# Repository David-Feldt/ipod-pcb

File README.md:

# E-ink Spotify iPod

A pocket Spotify remote with an e-paper screen. It shows what's playing (with
dithered album art), and its buttons and thumbwheel control playback and volume
on whichever device Spotify is playing on. It has no speaker or headphone jack.

## At a glance

| | |
|---|---|
| Chip | ESP32-S3-MINI-1-N8 (Wi-Fi + Bluetooth LE, 8 MB flash) |
| Screen | 2.13-inch GDEY0213B74 e-paper, 122 × 250, portrait |
| Controls | Five buttons and an absolute volume thumbwheel |
| Power | USB-C charging, 1S LiPo |
| Board | Revision E, 42 × 98 mm, four layers, four M2.5 mounting holes |
| Status | Board 1 is built and running the firmware |

## What it does

- **Now playing:** title, artist, progress and album art, from the Spotify Web API
  over Wi-Fi.
- **Controls:** play/pause, previous/next track, and wheel volume.
- **Easy setup:** a Wi-Fi setup hotspot, then Spotify sign-in from your phone.
- **Bluetooth fallback:** when Wi-Fi is out of range, it works as a Bluetooth
  media remote for your phone.
- **Battery care:** shows a "Battery low" screen and sleeps when the battery runs
  down.

## Repository guide

| Path | What's there |
|---|---|
| `firmware/remote/` | ESP-IDF application firmware: build and usage in its README |
| `kicad/` | KiCad 10 project, generated schematic and PCB, check reports |
| `gen/` | Python generators for the schematic, placement, routing and outputs |
| `fab/` | Gerbers, BOM, placement file, printable schematic, ordering notes |
| `pairing/` | Static sign-in bounce page used during Spotify pairing |
| `renders/`, `photos/` | Board renders and photos of the built device |
| `review/` | Hardware review evidence and datasheets |

| Document | Read it for |
|---|---|
| `DESIGN.md` | GPIO map, power architecture, revision notes |
| `FIRMWARE-NOTES.md` | Hardware rules the firmware must follow (charger, battery, wheel, display) |
| `BRINGUP.md` | Bring-up procedure and bench log |
| `DEBUG.md` | Debug links, pads and headers |
| `MECHANICAL.md` | Verified dimensions and enclosure fit |
| `ORDER-READINESS.md` | What must be checked before ordering boards |

## Getting started

```sh
git clone https://github.com/David-Feldt/ipod-pcb.git
cd ipod-pcb
```

Everything current is on `main`. The older 1.54-inch, 40 × 78 mm design is
tagged `v1-1.54in`. The `portrait-2.13` branch keeps the development history of
the 2.13-inch revision.

To open the board, close any running KiCad editors and open
`kicad/eink-pod.kicad_pro`.

## Rebuilding the board

Requires KiCad 10, Python 3, Java and `tools/freerouting.jar`.

```sh
./build.sh        # regenerate schematic, PCB, routing, fab files and renders
./check-order.sh  # pre-order gate: automated checks plus pending reviews
```

`build.sh` runs ERC, routing, DRC, schematic parity and critical-route checks,
and stops if any of them fails. Don't edit the generated KiCad files by hand:
the next build overwrites them. Edit the generators instead:

| Change | Edit |
|---|---|
| Circuit | `gen/build_sch.py` |
| Placement | `gen/build_pcb.py` |
| USB, decoupling and boost wiring | `gen/critical_routes.py` (checked by `gen/verify_board.py`) |

Don't run two builds at once or rebuild while an editor is saving the board.

## Ordering

Run `./check-order.sh` first and record external evidence in
`order-review.json`. Things to choose at the fab (details in `fab/README.md`):

- **Stackup:** JLC04161H-7628, four layers, 1.6 mm, with a 90-ohm differential
  target for USB.
- **Vias:** epoxy-filled and copper-capped. This design has vias in thermal pads,
  so ordinary tenting won't do.
- **Assembly:** both sides. Check every rotation in the assembler's preview
  against `fab/assembly-pin1.csv`. Take extra care with the MOSFETs, USB-C, FPC
  connector and slide switch.

| Layer | Use |
|---|---|
| F.Cu | Buttons, charge LED, USB pair, signals, GND pour |
| In1.Cu | GND plane, reference for the USB pair |
| In2.Cu | 3.3 V plane |
| B.Cu | Main components, signals, GND pour |

## Building and testing a board

- **Battery:** use a protected 1S LiPo rated for at least 250 mA charging, and
  check the JST lead polarity before plugging it in.
- **Mounting:** front screw heads or bosses at the top two holes must stay within
  4.5 mm diameter to clear the display glass. Use a nylon screw in the top-right
  hole, next to the antenna.
- **Test:** USB in both orientations, Wi-Fi during low battery and screen
  refresh, sleep current, charging temperature, and radio range in the assembled
  case.

See `BRINGUP.md` for the full procedure and `DEBUG.md` for the debug links and
headers.

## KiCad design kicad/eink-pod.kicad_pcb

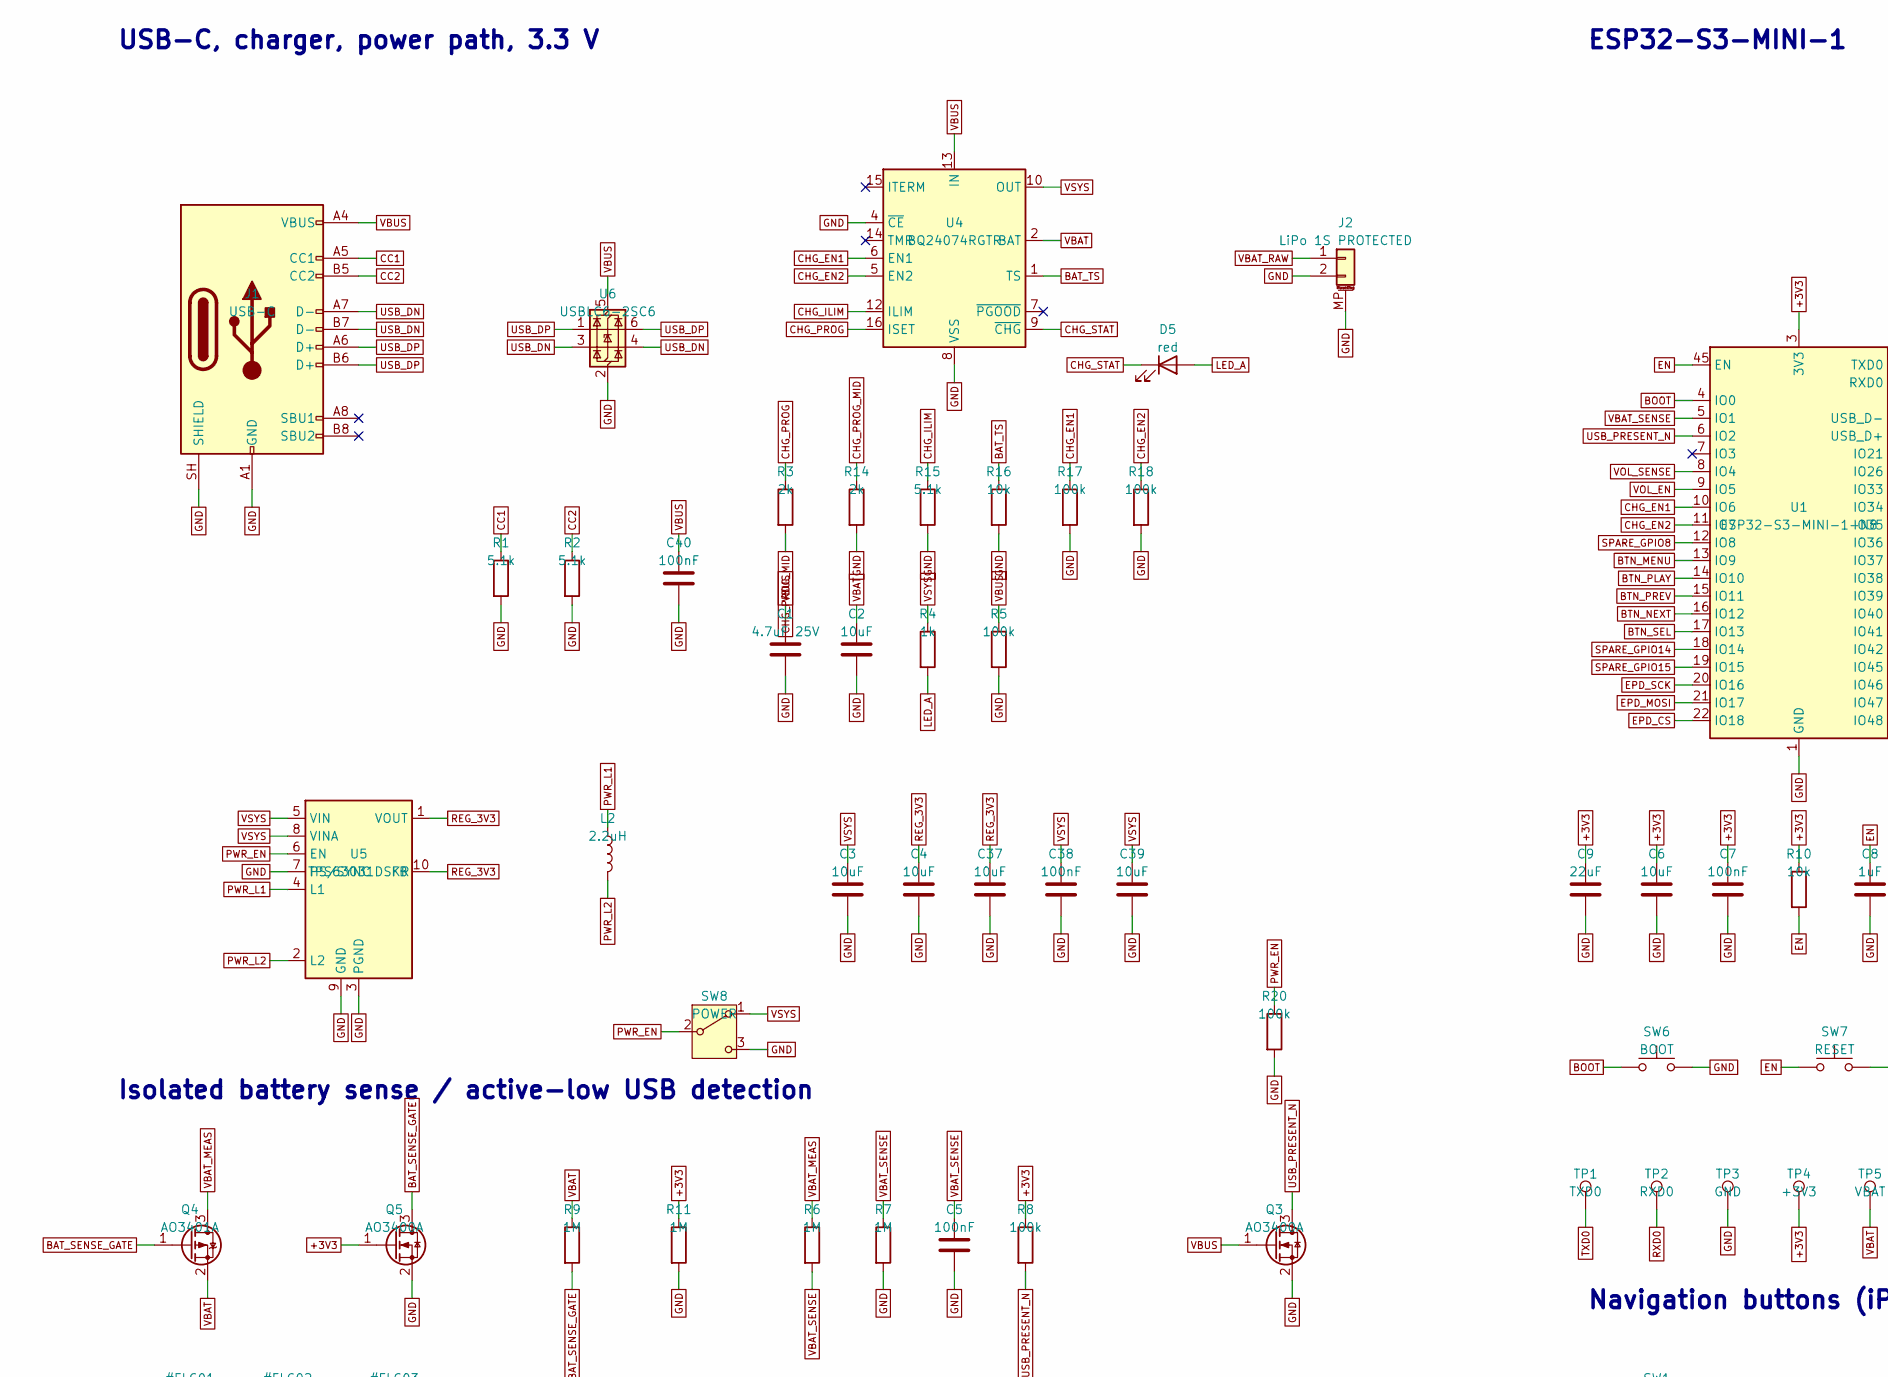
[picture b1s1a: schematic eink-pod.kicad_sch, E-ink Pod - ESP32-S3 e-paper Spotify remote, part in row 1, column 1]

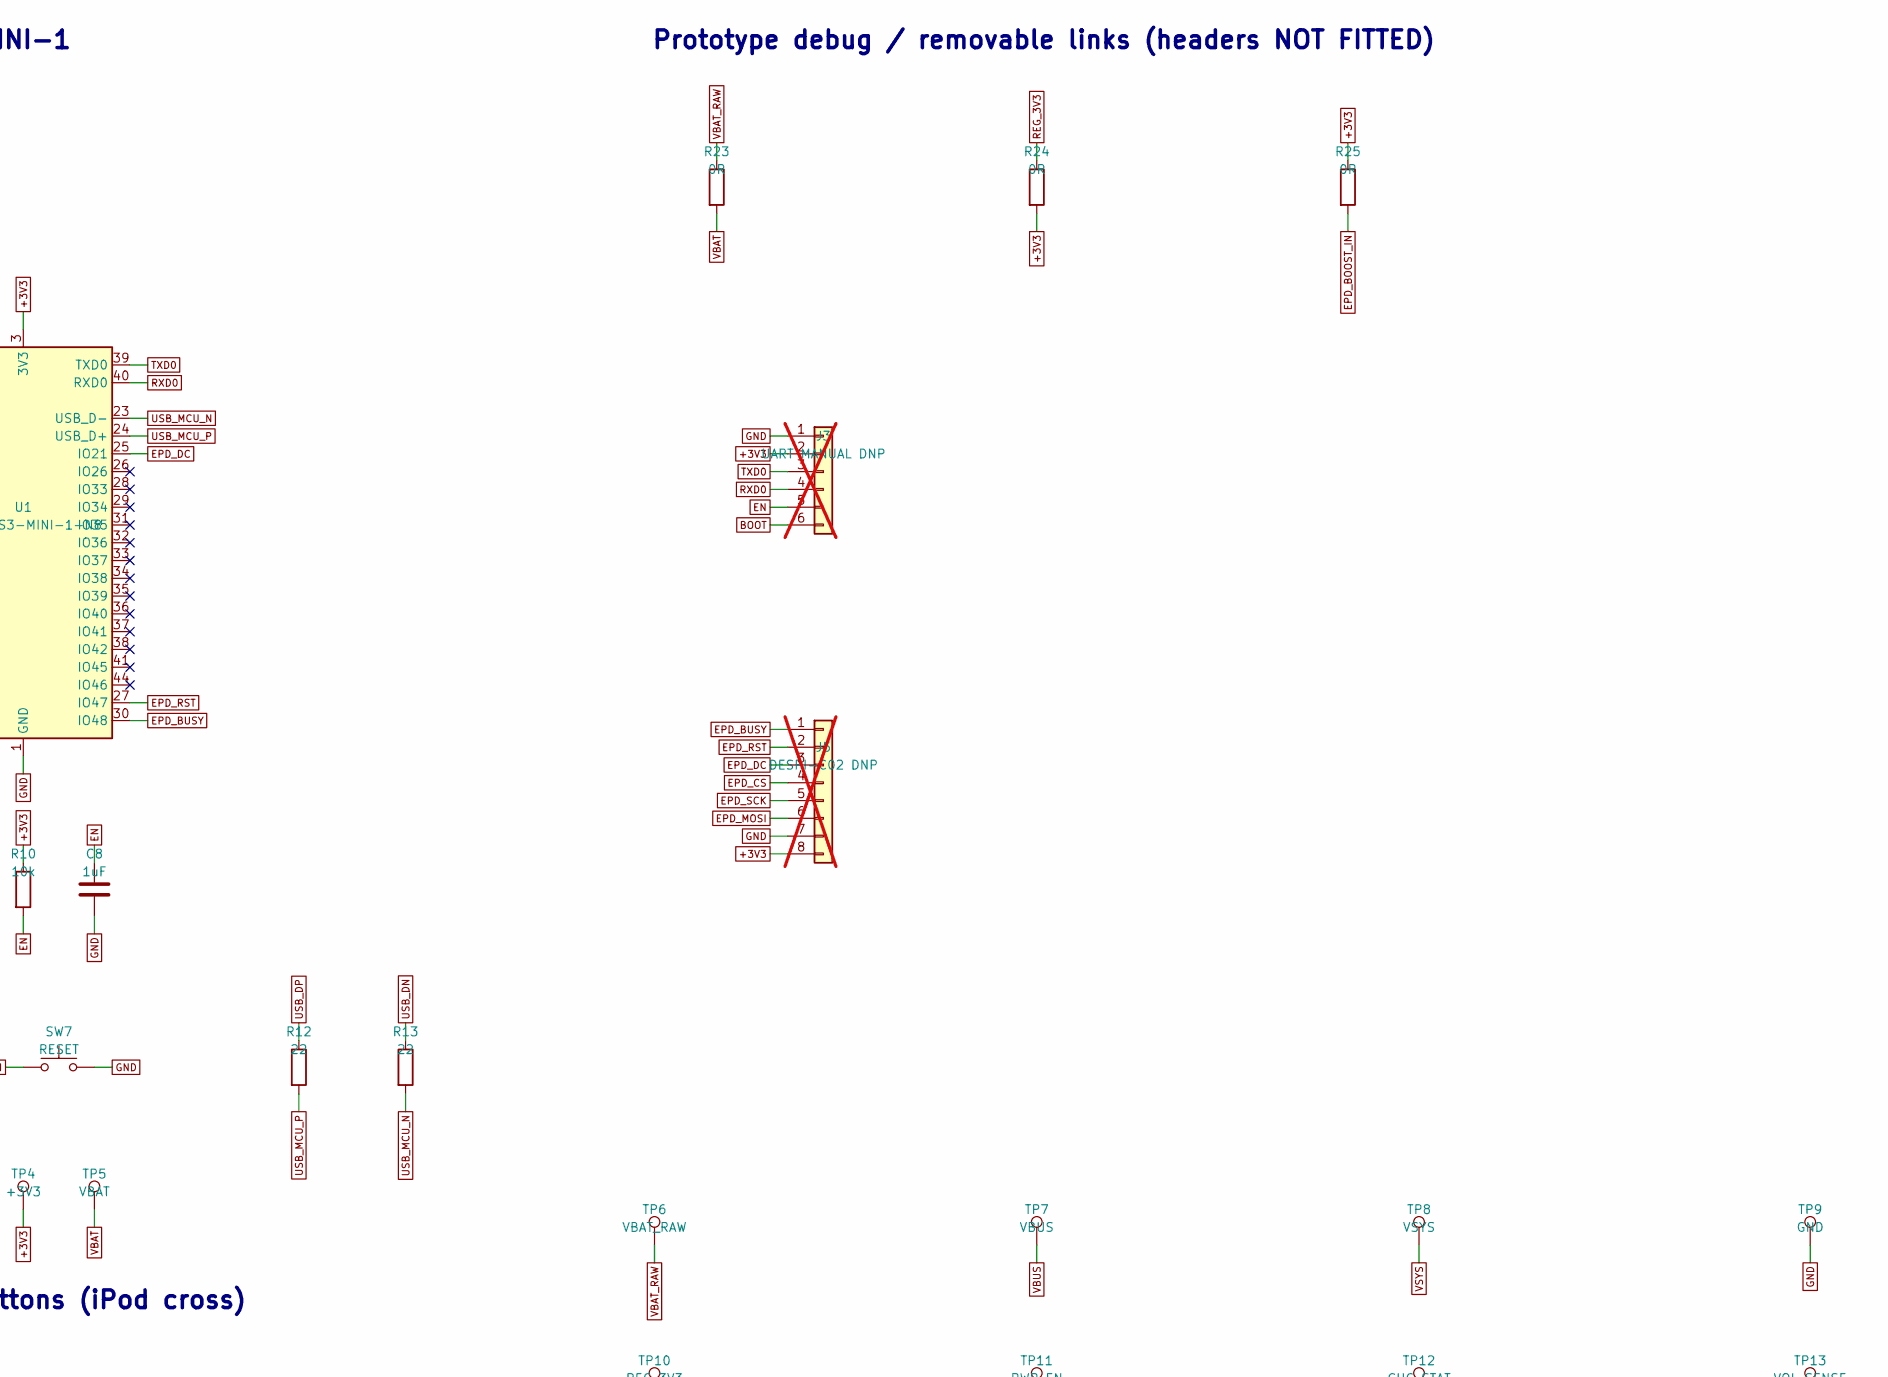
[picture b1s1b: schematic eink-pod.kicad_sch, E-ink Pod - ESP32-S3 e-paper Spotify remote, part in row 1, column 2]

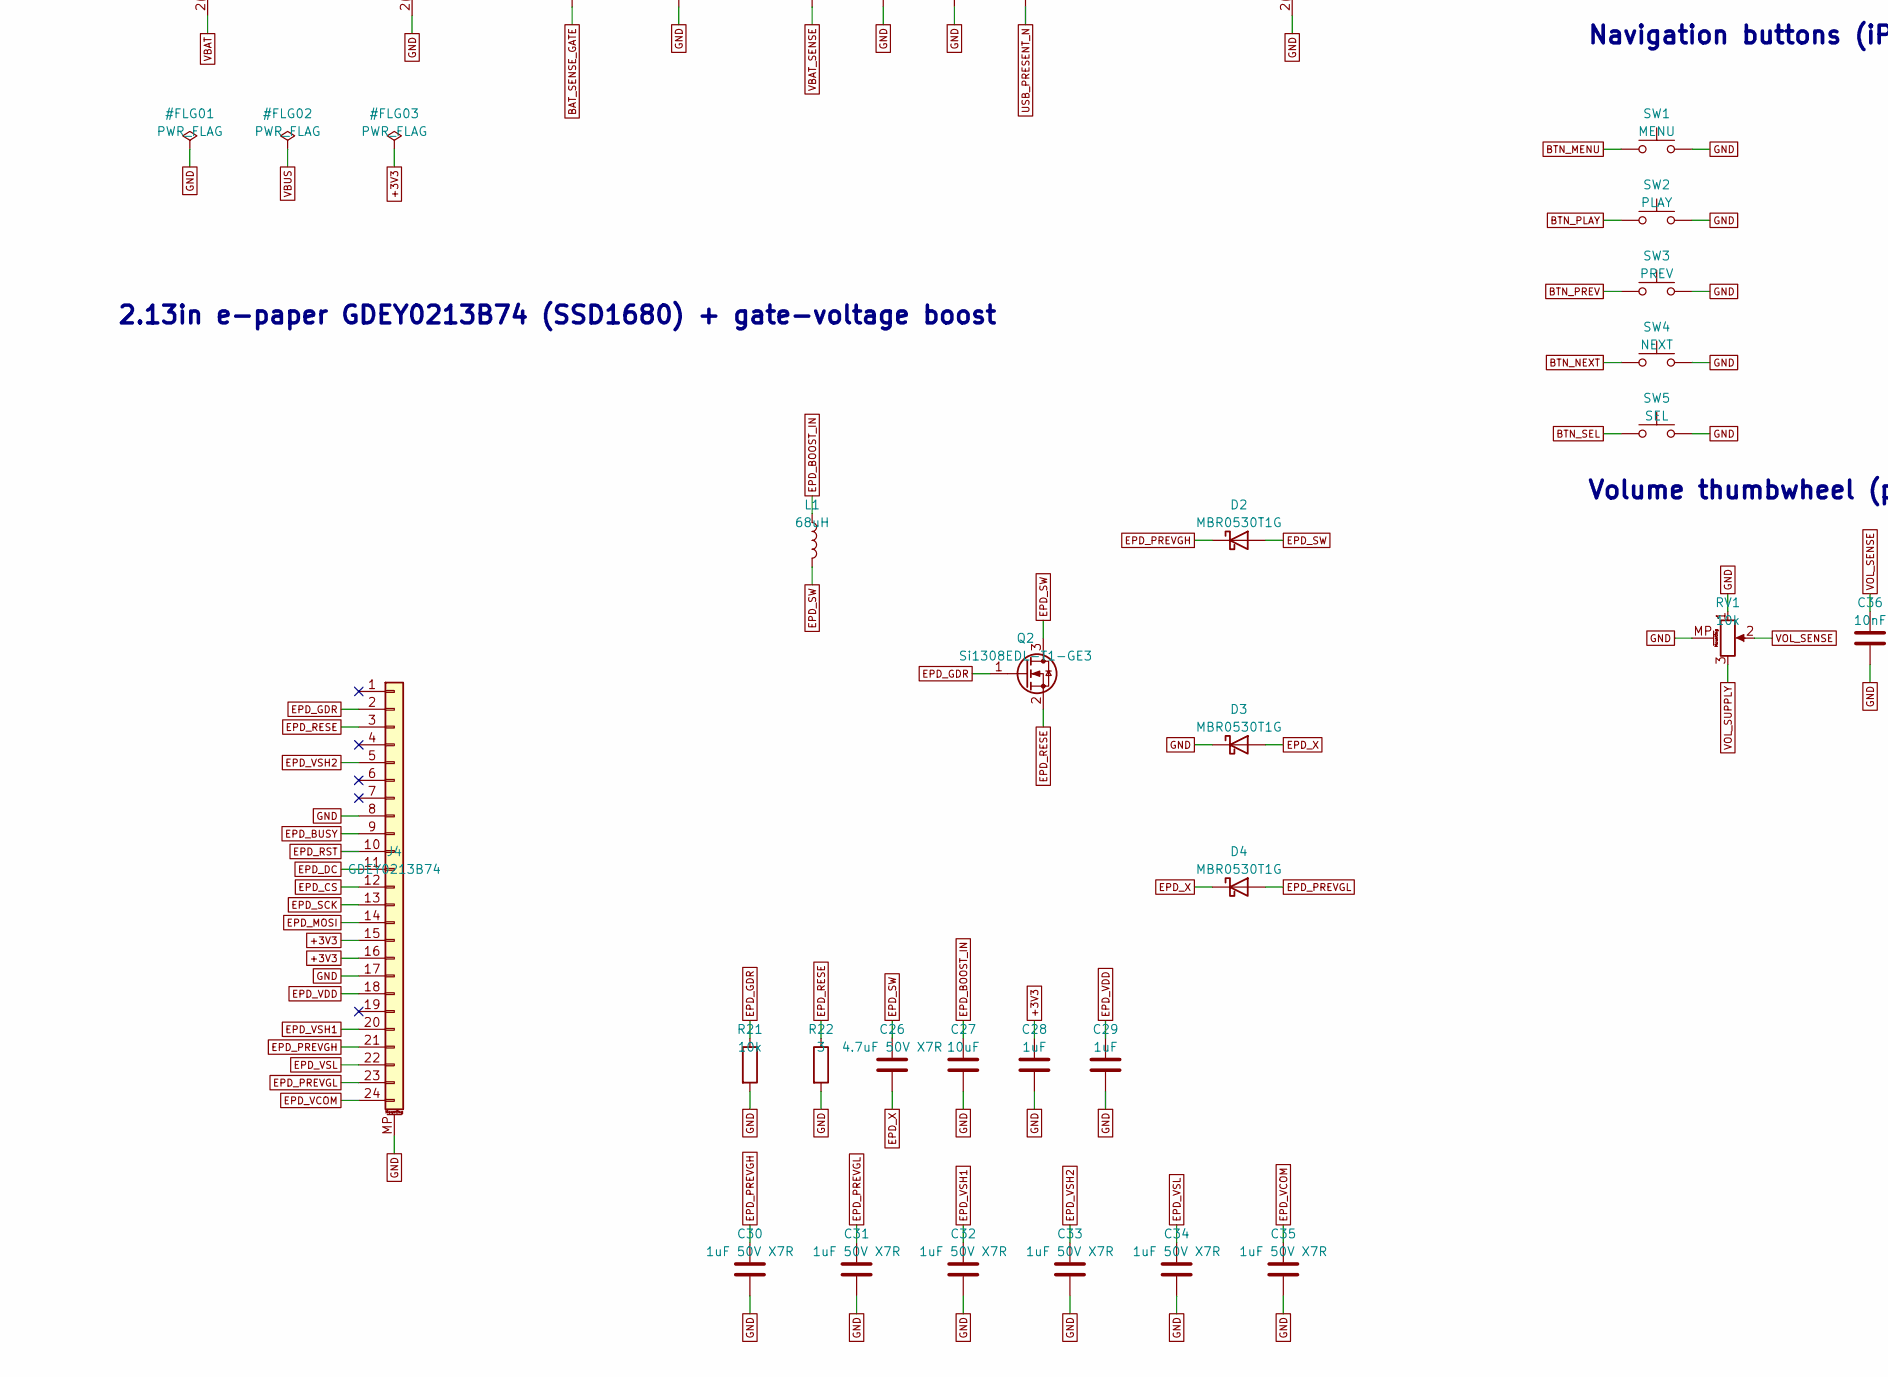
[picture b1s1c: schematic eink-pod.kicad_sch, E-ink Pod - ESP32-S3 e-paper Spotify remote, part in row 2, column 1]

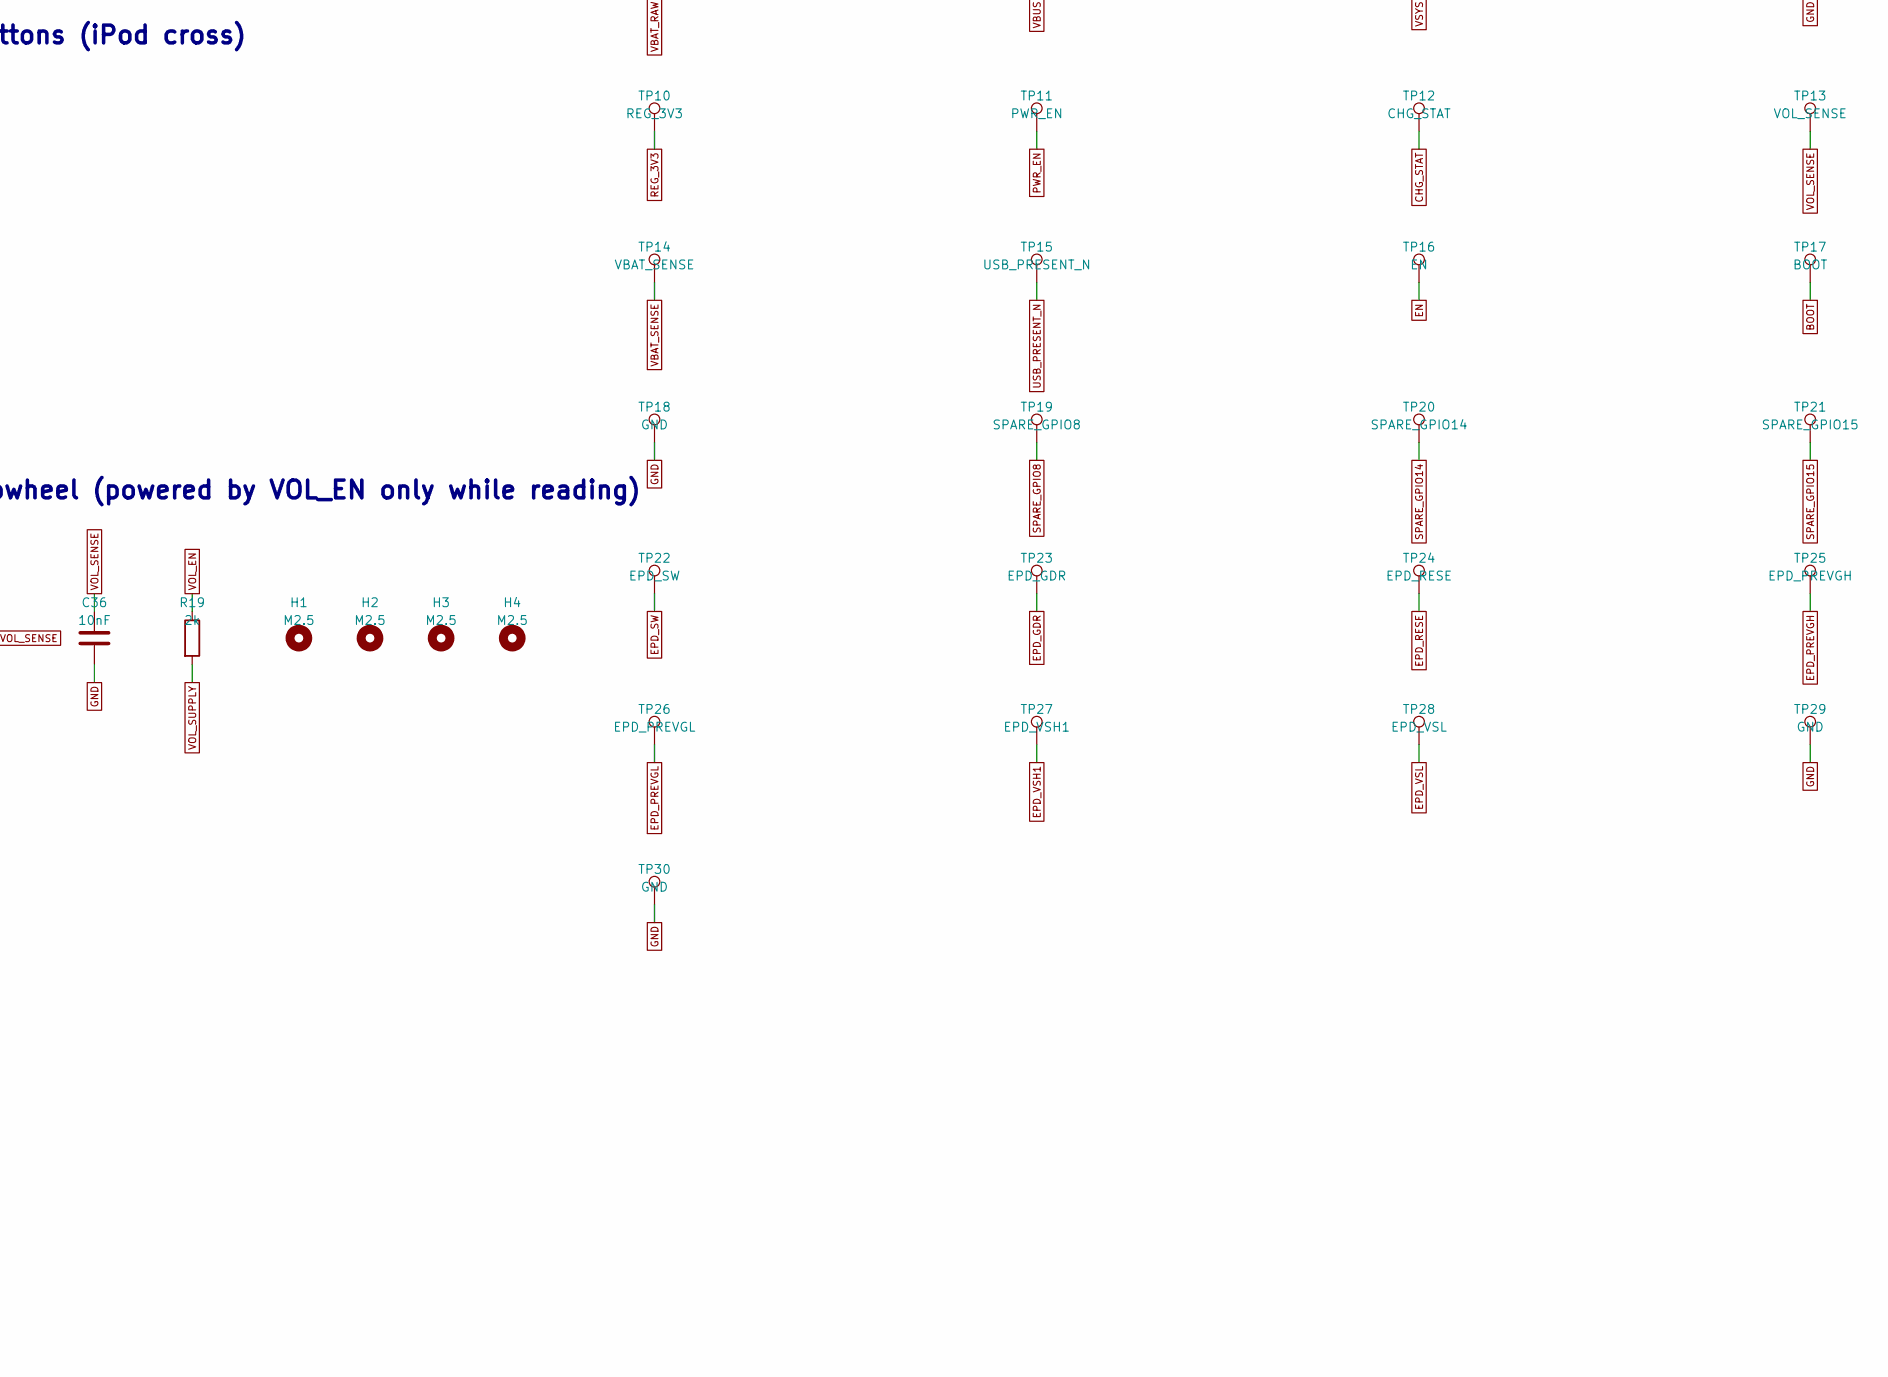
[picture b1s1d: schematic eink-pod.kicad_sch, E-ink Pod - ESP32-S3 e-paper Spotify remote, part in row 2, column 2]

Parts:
C1: 4.7uF 25V; C_0805_2012Metric; LCSC C1779
C2, C3, C4, C37, C39: 10uF; C_0805_2012Metric; LCSC C15850
C5, C7, C38, C40: 100nF; C_0402_1005Metric; LCSC C1525
C6, C27: 10uF; C_0603_1608Metric; LCSC C19702
C8, C28, C29: 1uF; C_0402_1005Metric; LCSC C52923
C9: 22uF; C_0603_1608Metric; LCSC C59461
C26: 4.7uF 50V X7R; C_1206_3216Metric; MPN CL31B475KBHNNNE; LCSC C51205
C30, C31, C32, C33, C34, C35: 1uF 50V X7R; C_0805_2012Metric; MPN CL21B105KBFNNNE; LCSC C28323
C36: 10nF; C_0402_1005Metric; LCSC C15195
D2, D3, D4: MBR0530T1G; D_SOD-123; MPN MBR0530T1G; LCSC C82046
D5: red; LED_0603_1608Metric; LCSC C2286
H1, H2, H3, H4: M2.5; MountingHole_2.7mm_M2.5
J1: USB-C; USB_C_Receptacle_HRO_TYPE-C-31-M-12; MPN TYPE-C-31-M-12; LCSC C165948
J2: LiPo 1S PROTECTED; JST_PH_S2B-PH-SM4-TB_1x02-1MP_P2.00mm_Horizontal; MPN S2B-PH-SM4-TB; LCSC C295747
J3: UART MANUAL DNP; PinHeader_1x06_P2.54mm_Vertical; not fitted
J4: GDEY0213B74; FPC-05FB-24PH20; MPN FPC-05FB-24PH20; LCSC C2856831
J5: DESPI-C02 DNP; PinHeader_1x08_P2.54mm_Vertical; not fitted
L1: 68uH; L_Sunlord_SWPA4030S; MPN SWPA4030S680MT; LCSC C83473
L2: 2.2uH; L_Sunlord_SWPA4030S; MPN SWPA4030S2R2MT; LCSC C36409
Q2: Si1308EDL-T1-GE3; SOT-323_SC-70; MPN Si1308EDL-T1-GE3; LCSC C469327
Q3, Q5: AO3400A; SOT-23; LCSC C20917
Q4: AO3401A; SOT-23; LCSC C15127
R1, R2, R15: 5.1k; R_0402_1005Metric; LCSC C25905
R3, R14, R19: 2k; R_0402_1005Metric; LCSC C4109
R4: 1k; R_0402_1005Metric; LCSC C11702
R5, R8, R17, R18, R20: 100k; R_0402_1005Metric; LCSC C25741
R6, R7, R9, R11: 1M; R_0402_1005Metric; LCSC C26083
R10, R16, R21: 10k; R_0402_1005Metric; LCSC C25744
R12, R13: 22; R_0402_1005Metric; LCSC C25092
R22: 3; R_0402_1005Metric; MPN 0402WGF300KTCE; LCSC C423196
R23, R24, R25: 0R; R_0805_2012Metric; MPN 0805W8F0000T5E; LCSC C17477
RV1: 10k; Alps_RK10J1xR_Thumbwheel; MPN RK10J11R0A0H; LCSC C470766
SW1: MENU; SW_SPST_TS-1088-xR020; LCSC C720477
SW2: PLAY; SW_SPST_TS-1088-xR020; LCSC C720477
SW3: PREV; SW_SPST_TS-1088-xR020; LCSC C720477
SW4: NEXT; SW_SPST_TS-1088-xR020; LCSC C720477
SW5: SEL; SW_SPST_TS-1088-xR020; LCSC C720477
SW6: BOOT; SW_SPST_TS-1088-xR020; LCSC C720477
SW7: RESET; SW_SPST_TS-1088-xR020; LCSC C720477
SW8: POWER; SW_SPDT_Shouhan_MSK12C02; LCSC C431540
TP1: TXD0; TestPoint_Pad_D1.0mm
TP2: RXD0; TestPoint_Pad_D1.0mm
TP3: GND; TestPoint_Pad_D1.0mm
TP4: +3V3; TestPoint_Pad_D1.0mm
TP5: VBAT; TestPoint_Pad_D1.0mm
TP6: VBAT_RAW; TestPoint_Pad_D1.0mm
TP7: VBUS; TestPoint_Pad_D1.0mm
TP8: VSYS; TestPoint_Pad_D1.0mm
TP9, TP18, TP29, TP30: GND; TestPoint_Pad_D1.5mm
TP10: REG_3V3; TestPoint_Pad_D1.0mm
TP11: PWR_EN; TestPoint_Pad_D1.0mm
TP12: CHG_STAT; TestPoint_Pad_D1.0mm
TP13: VOL_SENSE; TestPoint_Pad_D1.0mm
TP14: VBAT_SENSE; TestPoint_Pad_D1.0mm
TP15: USB_PRESENT_N; TestPoint_Pad_D1.0mm
TP16: EN; TestPoint_Pad_D1.0mm
TP17: BOOT; TestPoint_Pad_D1.0mm
TP19: SPARE_GPIO8; TestPoint_Pad_D1.0mm
TP20: SPARE_GPIO14; TestPoint_Pad_D1.0mm
TP21: SPARE_GPIO15; TestPoint_Pad_D1.0mm
TP22: EPD_SW; Probe_D0.6mm
TP23: EPD_GDR; Probe_D0.6mm
TP24: EPD_RESE; Probe_D0.6mm
TP25: EPD_PREVGH; Probe_D0.6mm
TP26: EPD_PREVGL; Probe_D0.6mm
TP27: EPD_VSH1; Probe_D0.6mm
TP28: EPD_VSL; Probe_D0.6mm
U1: ESP32-S3-MINI-1-N8; ESP32-S3-MINI-1; LCSC C2913206
U4: BQ24074RGTR; VQFN-16-1EP_3x3mm_P0.5mm_EP1.6x1.6mm; MPN BQ24074RGTR; LCSC C54313
U5: TPS63031DSKR; WSON-10-1EP_2.5x2.5mm_P0.5mm_EP1.2x2mm; MPN TPS63031DSKR; LCSC C15516
U6: USBLC6-2SC6; SOT-23-6; LCSC C7519

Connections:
+3V3: C6.1, C7.1, C9.1, C28.1, J3.2, J4.15, J4.16, J5.8, Q5.1 (G), R8.1, R10.1, R11.1, R24.2, R25.1, TP4.1, U1.3 (3V3)
BAT_SENSE_GATE: Q4.1 (G), Q5.3 (D), R9.2
BAT_TS: R16.1, U4.1 (TS)
BOOT: J3.6, SW6.1, TP17.1, U1.4 (IO0)
BTN_MENU: SW1.1, U1.13 (IO9)
BTN_NEXT: SW4.1, U1.16 (IO12)
BTN_PLAY: SW2.1, U1.14 (IO10)
BTN_PREV: SW3.1, U1.15 (IO11)
BTN_SEL: SW5.1, U1.17 (IO13)
CC1: J1.A5 (CC1), R1.1
CC2: J1.B5 (CC2), R2.1
CHG_EN1: R17.1, U1.10 (IO6), U4.6 (EN1)
CHG_EN2: R18.1, U1.11 (IO7), U4.5 (EN2)
CHG_ILIM: R15.1, U4.12 (ILIM)
CHG_PROG: R3.1, U4.16 (ISET)
CHG_PROG_MID: R3.2, R14.1
CHG_STAT: D5.1 (K), TP12.1, U4.9 (~CHG)
EN: C8.1, J3.5, R10.2, SW7.1, TP16.1, U1.45 (EN)
EPD_BOOST_IN: C27.1, L1.1, R25.2
EPD_BUSY: J4.9, J5.1, U1.30 (IO48)
EPD_CS: J4.12, J5.4, U1.22 (IO18)
EPD_DC: J4.11, J5.3, U1.25 (IO21)
EPD_GDR: J4.2, Q2.1 (G), R21.1, TP23.1
EPD_MOSI: J4.14, J5.6, U1.21 (IO17)
EPD_PREVGH: C30.1, D2.1 (K), J4.21, TP25.1
EPD_PREVGL: C31.1, D4.2 (A), J4.23, TP26.1
EPD_RESE: J4.3, Q2.2 (S), R22.1, TP24.1
EPD_RST: J4.10, J5.2, U1.27 (IO47)
EPD_SCK: J4.13, J5.5, U1.20 (IO16)
EPD_SW: C26.1, D2.2 (A), L1.2, Q2.3 (D), TP22.1
EPD_VCOM: C35.1, J4.24
EPD_VDD: C29.1, J4.18
EPD_VSH1: C32.1, J4.20, TP27.1
EPD_VSH2: C33.1, J4.5
EPD_VSL: C34.1, J4.22, TP28.1
EPD_X: C26.2, D3.2 (A), D4.1 (K)
GND: C1.2, C2.2, C3.2, C4.2, C5.2, C6.2, C7.2, C8.2, C9.2, C27.2, C28.2, C29.2, C30.2, C31.2, C32.2, C33.2, C34.2, C35.2, C36.2, C37.2, C38.2, C39.2, C40.2, D3.1 (K), J1.A1 (GND), J1.A12 (GND), J1.B1 (GND), J1.B12 (GND), J1.SH (SHIELD), J2.2, J2.MP (MountPin), J3.1, J4.8, J4.17, J4.MP (MountPin), J5.7, Q3.2 (S), Q5.2 (S), R1.2, R2.2, R5.2, R7.2, R11.2, R14.2, R15.2, R16.2, R17.2, R18.2, R20.2, R21.2, R22.2, RV1.1, RV1.MP (MountPin), SW1.2, SW2.2, SW3.2, SW4.2, SW5.2, SW6.2, SW7.2, SW8.3 (C), TP3.1, TP9.1, TP18.1, TP29.1, TP30.1, U1.1 (GND), U1.2 (GND), U1.42 (GND), U1.43 (GND), U1.46 (GND), U1.47 (GND), U1.48 (GND), U1.49 (GND), U1.50 (GND), U1.51 (GND), U1.52 (GND), U1.53 (GND), U1.54 (GND), U1.55 (GND), U1.56 (GND), U1.57 (GND), U1.58 (GND), U1.59 (GND), U1.60 (GND), U1.61 (GND), U1.62 (GND), U1.63 (GND), U1.64 (GND), U1.65 (GND), U4.4 (~CE), U4.8 (VSS), U4.17 (VSS), U5.3 (PGND), U5.7 (PS/SYNC), U5.9 (GND), U5.11 (PGND), U6.2 (GND)
LED_A: D5.2 (A), R4.2
PWR_EN: R20.1, SW8.2 (B), TP11.1, U5.6 (EN)
PWR_L1: L2.1, U5.4 (L1)
PWR_L2: L2.2, U5.2 (L2)
REG_3V3: C4.1, C37.1, R24.1, TP10.1, U5.1 (VOUT), U5.10 (FB)
RXD0: J3.4, TP2.1, U1.40 (RXD0)
SPARE_GPIO8: TP19.1, U1.12 (IO8)
SPARE_GPIO14: TP20.1, U1.18 (IO14)
SPARE_GPIO15: TP21.1, U1.19 (IO15)
TXD0: J3.3, TP1.1, U1.39 (TXD0)
USB_DN: J1.A7 (D-), J1.B7 (D-), R13.1, U6.3 (I/O2), U6.4 (I/O2)
USB_DP: J1.A6 (D+), J1.B6 (D+), R12.1, U6.1 (I/O1), U6.6 (I/O1)
USB_MCU_N: R13.2, U1.23 (USB_D-)
USB_MCU_P: R12.2, U1.24 (USB_D+)
USB_PRESENT_N: Q3.3 (D), R8.2, TP15.1, U1.6 (IO2)
VBAT: C2.1, Q4.2 (S), R9.1, R23.2, TP5.1, U4.2 (BAT), U4.3 (BAT)
VBAT_MEAS: Q4.3 (D), R6.1
VBAT_RAW: J2.1, R23.1, TP6.1
VBAT_SENSE: C5.1, R6.2, R7.1, TP14.1, U1.5 (IO1)
VBUS: C1.1, C40.1, J1.A4 (VBUS), J1.A9 (VBUS), J1.B4 (VBUS), J1.B9 (VBUS), Q3.1 (G), R5.1, TP7.1, U4.13 (IN), U6.5 (VBUS)
VOL_EN: R19.1, U1.9 (IO5)
VOL_SENSE: C36.1, RV1.2, TP13.1, U1.8 (IO4)
VOL_SUPPLY: R19.2, RV1.3
VSYS: C3.1, C38.1, C39.1, R4.1, SW8.1 (A), TP8.1, U4.10 (OUT), U4.11 (OUT), U5.5 (VIN), U5.8 (VINA)

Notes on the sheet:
USB-C, charger, power path, 3.3 V
Isolated battery sense / active-low USB detection
ESP32-S3-MINI-1
Navigation buttons (iPod cross)
Volume thumbwheel (powered by VOL_EN only while reading)
2.13in e-paper GDEY0213B74 (SSD1680) + gate-voltage boost
Prototype debug / removable links (headers NOT FITTED)

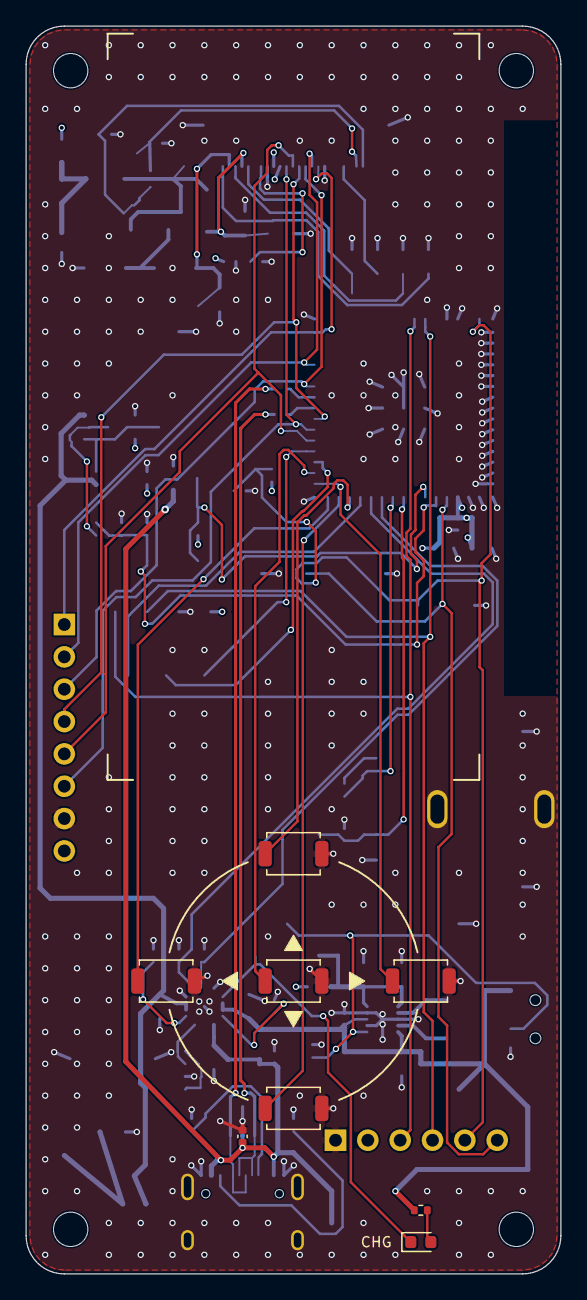
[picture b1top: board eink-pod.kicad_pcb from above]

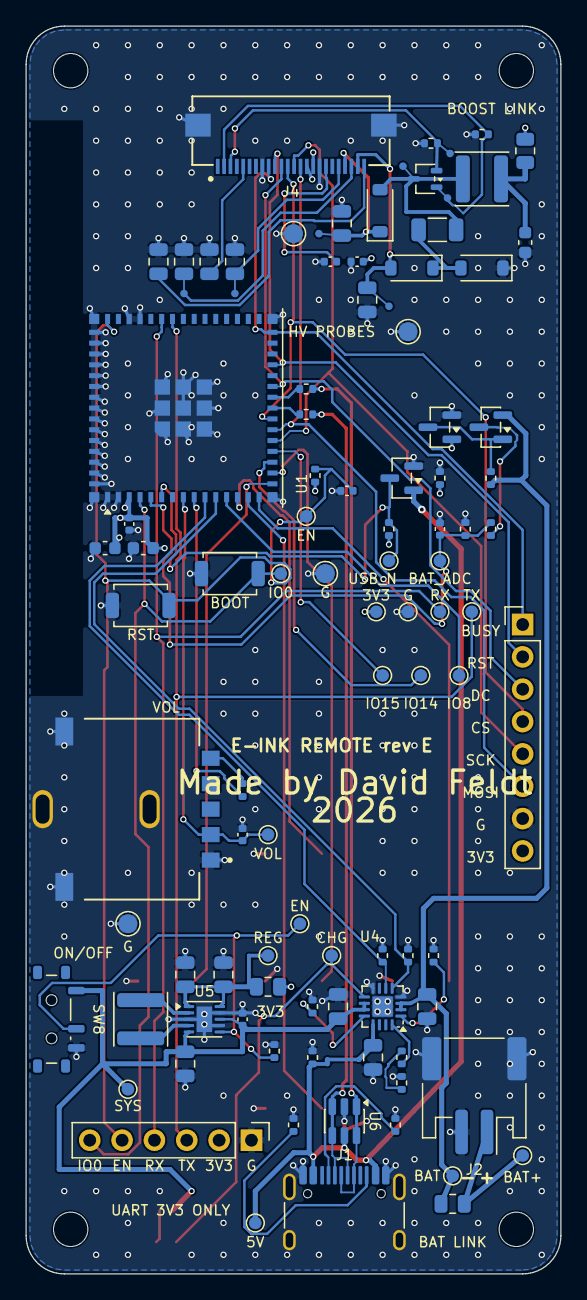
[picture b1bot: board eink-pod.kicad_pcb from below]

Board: 4 copper layers, 42.0 x 98.0 mm, 112 parts (103 on the bottom side), 61 nets.

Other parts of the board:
DS1: GDEY0213B74; EPD_GDEY0213B74_3D

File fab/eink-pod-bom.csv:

Comment,Designator,Footprint,LCSC Part #,Qty
4.7uF 25V,C1,C_0805_2012Metric,C1779,1
10uF,"C2,C3,C4,C37,C39",C_0805_2012Metric,C15850,5
100nF,"C5,C7,C38,C40",C_0402_1005Metric,C1525,4
10uF,"C6,C27",C_0603_1608Metric,C19702,2
1uF,"C8,C28,C29",C_0402_1005Metric,C52923,3
22uF,C9,C_0603_1608Metric,C59461,1
4.7uF 50V X7R,C26,C_1206_3216Metric,C51205,1
1uF 50V X7R,"C30,C31,C32,C33,C34,C35",C_0805_2012Metric,C28323,6
10nF,C36,C_0402_1005Metric,C15195,1
MBR0530T1G,"D2,D3,D4",D_SOD-123,C82046,3
red,D5,LED_0603_1608Metric,C2286,1
USB-C,J1,USB_C_Receptacle_HRO_TYPE-C-31-M-12,C165948,1
LiPo 1S PROTECTED,J2,JST_PH_S2B-PH-SM4-TB_1x02-1MP_P2.00mm_Horizontal,C295747,1
GDEY0213B74,J4,FPC-05FB-24PH20,C2856831,1
68uH,L1,L_Sunlord_SWPA4030S,C83473,1
2.2uH,L2,L_Sunlord_SWPA4030S,C36409,1
Si1308EDL-T1-GE3,Q2,SOT-323_SC-70,C469327,1
AO3400A,"Q3,Q5",SOT-23,C20917,2
AO3401A,Q4,SOT-23,C15127,1
5.1k,"R1,R2,R15",R_0402_1005Metric,C25905,3
2k,"R3,R14,R19",R_0402_1005Metric,C4109,3
1k,R4,R_0402_1005Metric,C11702,1
100k,"R5,R8,R17,R18,R20",R_0402_1005Metric,C25741,5
1M,"R6,R7,R9,R11",R_0402_1005Metric,C26083,4
10k,"R10,R16,R21",R_0402_1005Metric,C25744,3
22,"R12,R13",R_0402_1005Metric,C25092,2
3,R22,R_0402_1005Metric,C423196,1
0R,"R23,R24,R25",R_0805_2012Metric,C17477,3
10k,RV1,Alps_RK10J1xR_Thumbwheel,C470766,1
BOOT/RESET/MENU/PLAY/PREV/NEXT/SEL,"SW1,SW2,SW3,SW4,SW5,SW6,SW7",SW_SPST_TS-1088-xR020,C720477,7
POWER,SW8,SW_SPDT_Shouhan_MSK12C02,C431540,1
ESP32-S3-MINI-1-N8,U1,ESP32-S3-MINI-1,C2913206,1
BQ24074RGTR,U4,VQFN-16-1EP_3x3mm_P0.5mm_EP1.6x1.6mm,C54313,1
TPS63031DSKR,U5,WSON-10-1EP_2.5x2.5mm_P0.5mm_EP1.2x2mm,C15516,1
USBLC6-2SC6,U6,SOT-23-6,C7519,1

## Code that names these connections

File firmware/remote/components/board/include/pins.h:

// GPIO map for the rev E board. Source of truth: DESIGN.md "GPIO map";
// matches firmware/bringup and firmware/display_test.
#pragma once

#define PIN_VBAT_SENSE     1   // ADC1_CH0, 1M/1M divider -> multiply by 2
#define PIN_USB_PRESENT_N  2   // LOW = VBUS present; external pull-up R8, no internal pulls
#define PIN_VOL_SENSE      4   // ADC1_CH3, wheel wiper
#define PIN_VOL_EN         5   // powers the wheel pot only while reading
#define PIN_CHG_EN1        6   // BQ24074 EN1 (100k pull-down)
#define PIN_CHG_EN2        7   // BQ24074 EN2 (100k pull-down)

#define PIN_BTN_MENU       9   // buttons: active LOW, firmware pull-ups
#define PIN_BTN_PLAY       10
#define PIN_BTN_PREV       11
#define PIN_BTN_NEXT       12
#define PIN_BTN_SEL        13
#define PIN_BTN_BOOT       0

#define PIN_EPD_SCK        16
#define PIN_EPD_MOSI       17
#define PIN_EPD_CS         18
#define PIN_EPD_DC         21
#define PIN_EPD_RST        47
#define PIN_EPD_BUSY       48  // HIGH = busy

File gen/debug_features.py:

"""Revision E debug access: names, net assignments and board-local placement."""
# ref: (net, x, y, pad diameter mm). Existing TP1-TP5 are retained.
POINTS = {
 'TP6': ('VBAT_RAW',3,88.7,1.0),
 'TP7': ('VBUS',24,94,1.0),
 'TP8': ('VSYS',34,83.5,1.0),
 'TP9': ('GND',34,70.5,1.5),
 'TP10': ('REG_3V3',23,73,1.0),
 'TP11': ('PWR_EN',20.5,70.5,1.0),
 'TP12': ('CHG_STAT',18,73,1.0),
 'TP13': ('VOL_SENSE',23,63.5,1.0),
 'TP14': ('VBAT_SENSE',9.5,42,1.0),
 'TP15': ('USB_PRESENT_N',13.5,42,1.0),
 'TP16': ('EN',20,38.5,1.0),
 'TP17': ('BOOT',22,43,1.0),
 'TP18': ('GND',18.5,43,1.5),
 'TP19': ('SPARE_GPIO8',8,51,1.0),
 'TP20': ('SPARE_GPIO14',11,51,1.0),
 'TP21': ('SPARE_GPIO15',14,51,1.0),
 'TP22': ('EPD_SW',12.4,11,0.6),
 'TP23': ('EPD_GDR',8.9,13.5,0.6),
 'TP24': ('EPD_RESE',8.7,10,0.6),
 'TP25': ('EPD_PREVGH',19,16.3,0.6),
 'TP26': ('EPD_PREVGL',13.5,22,0.6),
 'TP27': ('EPD_VSH1',25.6,21,0.6),
 'TP28': ('EPD_VSL',29.6,21,0.6),
 'TP29': ('GND',21,16.3,1.5),
 'TP30': ('GND',12,24,1.5),
}
PROGRAM = ['GND', '+3V3', 'TXD0', 'RXD0', 'EN', 'BOOT']
# Good Display DESPI-C02 user manual pins 1..8; connect by signal labels.
DISPLAY = ['EPD_BUSY','EPD_RST','EPD_DC','EPD_CS','EPD_SCK','EPD_MOSI','GND','+3V3']
# Keep high-impedance/switching-node probes local, with no autorouted branches.
PROBE_ANCHORS = {'TP22':('Q2',3), 'TP23':('Q2',1), 'TP24':('R22',1),
                 'TP25':('C30',1), 'TP26':('C31',1), 'TP27':('C32',1), 'TP28':('C34',1)}
